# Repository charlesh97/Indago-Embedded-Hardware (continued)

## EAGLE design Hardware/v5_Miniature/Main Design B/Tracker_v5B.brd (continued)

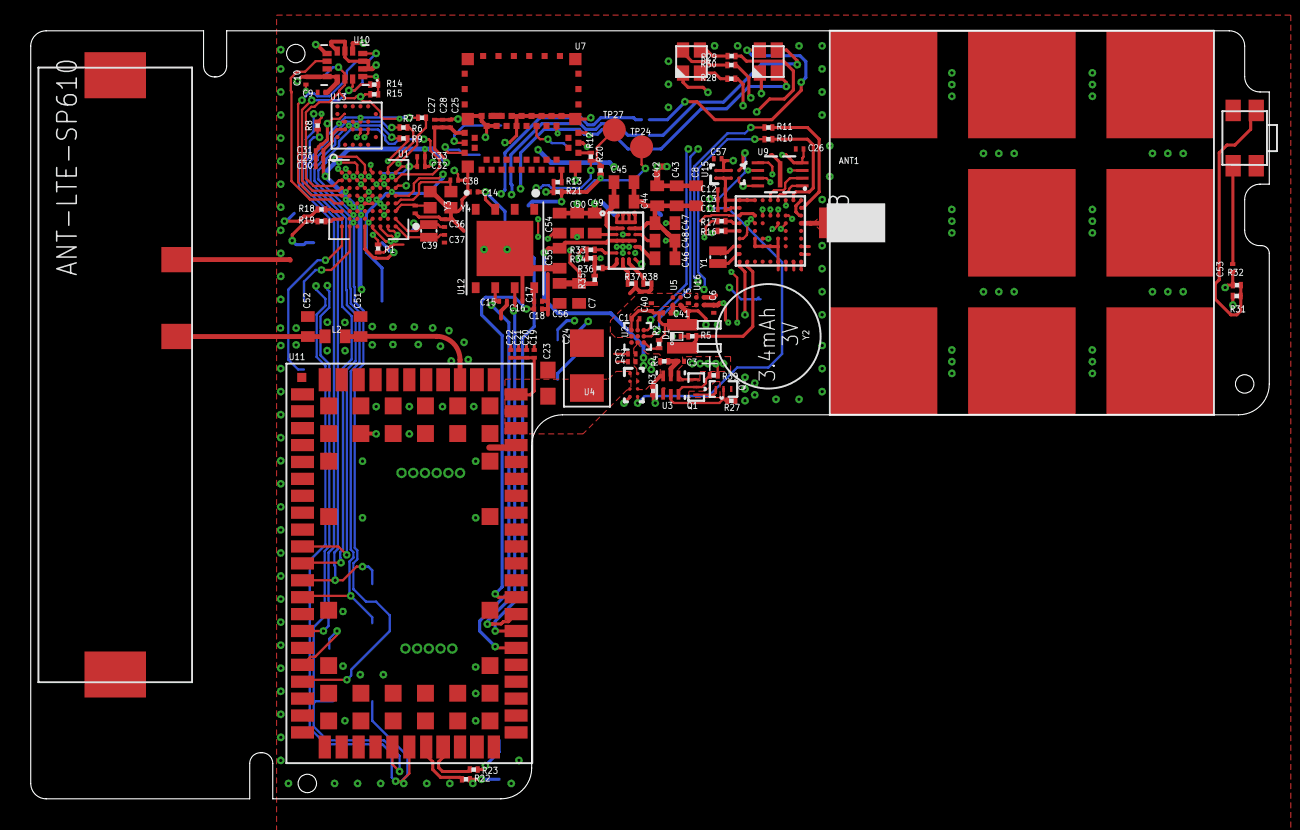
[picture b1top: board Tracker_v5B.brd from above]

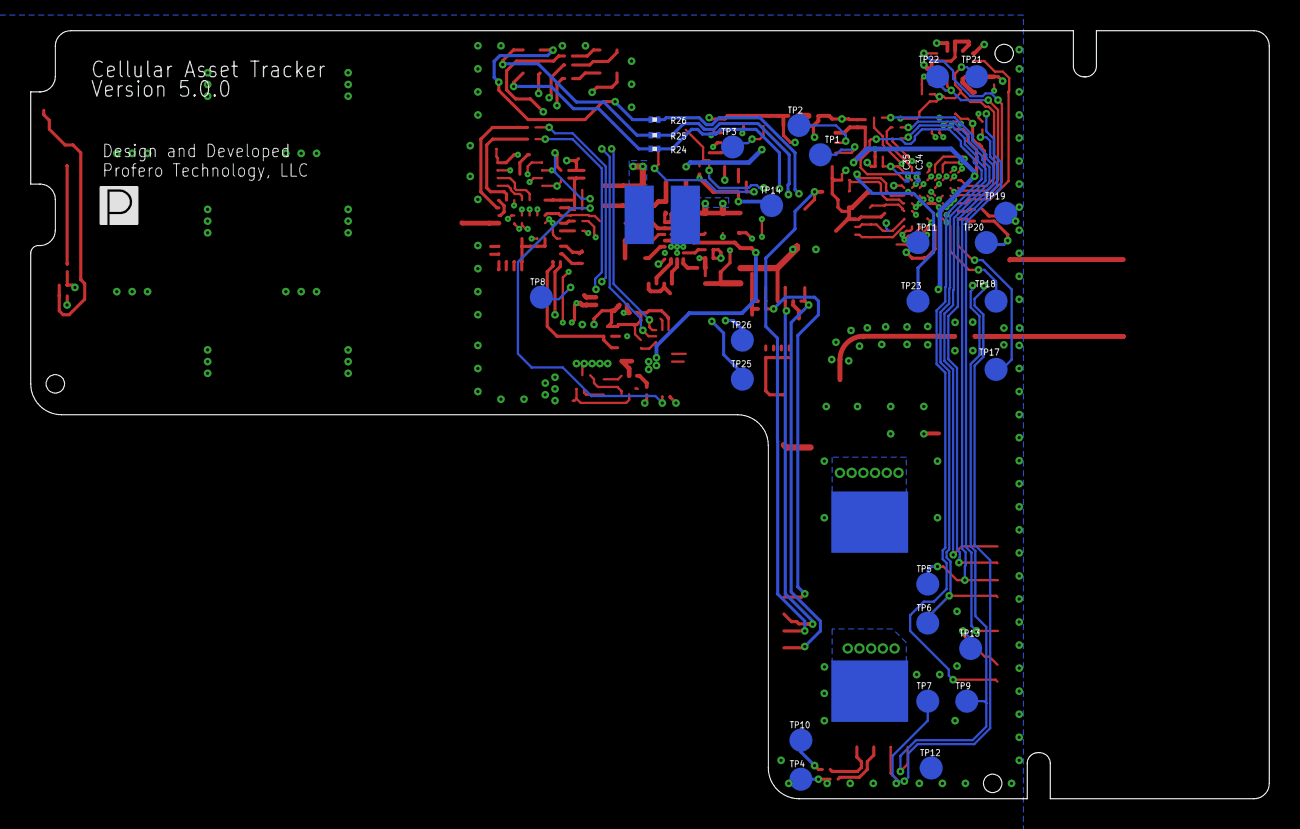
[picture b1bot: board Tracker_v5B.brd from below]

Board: 4 copper layers, 80.6 x 50.0 mm, 154 parts (33 on the bottom side), 124 nets.

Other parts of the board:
U$2: PROFERO-LOGO-SMALL

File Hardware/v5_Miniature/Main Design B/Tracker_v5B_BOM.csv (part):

"Qty";"Value";"Device";"Package";"Parts";"Description";"ALTERNATE_PARTNUMBER";"APPLICATION_BUILDNUMBER";"BOI";"BOI-METRIC";"BUILT_BY";"CATEGORY";"COMPTYPE";"COPYRIGHT";"CREATED_BY";"DESCRIPTION";"DESIG";"DIGI#";"DIGI-KEY_PART_NUMBER";"DIGI-KEY_PURCHASE_URL";"DIGIKEY_PART_NUMBER";"FAB";"ISP_PART";"MANF#";"MANUFACTURER";"MANUFACTURER_PART_NUMBER";"MF";"MOUNTTYPE";"MP";"MPN";"OPERATING_TEMP";"PACKAGE";"PACKAGEREFERENCE";"PARTNUMBER";"PART_STATUS";"PIN_COUNT";"POPULARITY";"REF";"REFDES";"ROHS";"ROHS_COMPLIANT";"SERIES";"SOURCELIBRARY";"SPICEPREFIX";"SUB-CATEGORY";"THERMALLOSS";"TP_SIGNAL_NAME";"TYPE";"URL";"VALUE";"VENDOR";"VOLTAGE_RATING";
"12";"0.1uF";"C-EUC0201";"C0201";"C2, C3, C9, C10, C11, C17, C22, C25, C26, C27, C32, C34";"CAPACITOR, European symbol";"";"";"";"";"";"";"";"";"";"";"";"";"";"";"";"";"";"";"";"";"";"";"";"";"";"";"";"";"";"";"0";"";"";"";"";"";"";"C";"";"";"";"";"";"";"";"";
"1";"0.47uF";"C-EUC0201";"C0201";"C1";"CAPACITOR, European symbol";"";"";"";"";"";"";"";"";"";"";"";"";"";"";"";"";"";"";"";"";"";"";"";"";"";"";"";"";"";"";"0";"";"";"";"";"";"";"C";"";"";"";"";"";"";"";"";
"1";"0ohm";"C-EUC0402";"C0402";"L2";"CAPACITOR, European symbol";"";"";"";"";"";"";"";"";"";"";"";"";"";"";"";"";"";"";"";"";"";"";"";"";"";"";"";"";"";"";"18";"";"";"";"";"";"";"C";"";"";"";"";"";"";"";"";
"1";"1.8nF";"C-EUC0402";"C0402";"C45";"CAPACITOR, European symbol";"";"";"";"";"";"";"";"";"";"";"";"";"";"";"";"";"";"";"";"";"";"";"";"";"";"";"";"";"";"";"18";"";"";"";"";"";"";"C";"";"";"";"";"";"";"";"";
"8";"100";"R-US_R0201";"R0201";"R6, R7, R8, R9, R12, R13, R16, R17";"RESISTOR, American symbol";"";"";"";"";"";"";"";"";"";"";"";"";"";"";"";"";"";"";"";"";"";"";"";"";"";"";"";"";"";"";"0";"";"";"";"";"";"";"R";"";"";"";"";"";"";"";"";
"7";"10000pF";"C-EUC0201";"C0201";"C13, C21, C29, C30, C31, C33, C35";"CAPACITOR, European symbol";"";"";"";"";"";"";"";"";"";"";"";"";"";"";"";"";"";"";"";"";"";"";"";"";"";"";"";"";"";"";"0";"";"";"";"";"";"";"C";"";"";"";"";"";"";"";"";
"3";"100k";"R-US_R0201";"R0201";"R1, R31, R32";"RESISTOR, American symbol";"";"";"";"";"";"";"";"";"";"";"";"";"";"";"";"";"";"";"";"";"";"";"";"";"";"";"";"";"";"";"0";"";"";"";"";"";"";"R";"";"";"";"";"";"";"";"";
"1";"100pF";"C-EUC0201";"C0201";"C53";"CAPACITOR, European symbol";"";"";"";"";"";"";"";"";"";"";"";"";"";"";"";"";"";"";"";"";"";"";"";"";"";"";"";"";"";"";"0";"";"";"";"";"";"";"C";"";"";"";"";"";"";"";"";
"1";"100pF";"C-EUC0402";"C0402";"C44";"CAPACITOR, European symbol";"";"";"";"";"";"";"";"";"";"";"";"";"";"";"";"";"";"";"";"";"";"";"";"";"";"";"";"";"";"";"18";"";"";"";"";"";"";"C";"";"";"";"";"";"";"";"";
"3";"10k";"R-US_R0201";"R0201";"R2, R33, R37";"RESISTOR, American symbol";"";"";"";"";"";"";"";"";"";"";"";"";"";"";"";"";"";"";"";"";"";"";"";"";"";"";"";"";"";"";"0";"";"";"";"";"";"";"R";"";"";"";"";"";"";"";"";
"2";"10nF";"C-EUC0402";"C0402";"C48, C49";"CAPACITOR, European symbol";"";"";"";"";"";"";"";"";"";"";"";"";"";"";"";"";"";"";"";"";"";"";"";"";"";"";"";"";"";"";"18";"";"";"";"";"";"";"C";"";"";"";"";"";"";"";"";
"2";"10pF";"C-EUC0201";"C0201";"C38, C39";"CAPACITOR, European symbol";"";"";"";"";"";"";"";"";"";"";"";"";"";"";"";"";"";"";"";"";"";"";"";"";"";"";"";"";"";"";"0";"";"";"";"";"";"";"C";"";"";"";"";"";"";"";"";
"1";"10uF";"C-EUC0402";"C0402";"C7";"CAPACITOR, European symbol";"";"";"";"";"";"";"";"";"";"";"";"";"";"";"";"";"";"";"";"";"";"";"";"";"";"";"";"";"";"";"18";"";"";"";"";"";"";"C";"";"";"";"";"";"";"";"";
"1";"10uF";"C-EUC0603";"C0603";"C23";"CAPACITOR, European symbol";"";"";"";"";"";"";"";"";"";"";"";"";"";"";"";"";"";"";"";"";"";"";"";"";"";"";"";"";"";"";"73";"";"";"";"";"";"";"C";"";"";"";"";"";"";"";"";
"2";"130";"R-US_R0201";"R0201";"R24, R28";"RESISTOR, American symbol";"";"";"";"";"";"";"";"";"";"";"";"";"";"";"";"";"";"";"";"";"";"";"";"";"";"";"";"";"";"";"0";"";"";"";"";"";"";"R";"";"";"";"";"";"";"";"";
"3";"15pF";"C-EUC0201";"C0201";"C19, C36, C37";"CAPACITOR, European symbol";"";"";"";"";"";"";"";"";"";"";"";"";"";"";"";"";"";"";"";"";"";"";"";"";"";"";"";"";"";"";"0";"";"";"";"";"";"";"C";"";"";"";"";"";"";"";"";
"1";"196ohm";"R-US_R0201";"R0201";"R34";"RESISTOR, American symbol";"";"";"";"";"";"";"";"";"";"";"";"";"";"";"";"";"";"";"";"";"";"";"";"";"";"";"";"";"";"";"0";"";"";"";"";"";"";"R";"";"";"";"";"";"";"";"";
"1";"1k";"R-US_R0201";"R0201";"R5";"RESISTOR, American symbol";"";"";"";"";"";"";"";"";"";"";"";"";"";"";"";"";"";"";"";"";"";"";"";"";"";"";"";"";"";"";"0";"";"";"";"";"";"";"R";"";"";"";"";"";"";"";"";
"8";"1uF";"C-EUC0201";"C0201";"C4, C5, C6, C12, C28, C40, C41, C57";"CAPACITOR, European symbol";"";"";"";"";"";"";"";"";"";"";"";"";"";"";"";"";"";"";"";"";"";"";"";"";"";"";"";"";"";"";"0";"";"";"";"";"";"";"C";"";"";"";"";"";"";"";"";
"2";"2.2uF";"C-EUC0402";"C0402";"C55, C56";"CAPACITOR, European symbol";"";"";"";"";"";"";"";"";"";"";"";"";"";"";"";"";"";"";"";"";"";"";"";"";"";"";"";"";"";"";"18";"";"";"";"";"";"";"C";"";"";"";"";"";"";"";"";
"1";"2.4k";"R-US_R0201";"R0201";"R38";"RESISTOR, American symbol";"";"";"";"";"";"";"";"";"";"";"";"";"";"";"";"";"";"";"";"";"";"";"";"";"";"";"";"";"";"";"0";"";"";"";"";"";"";"R";"";"";"";"";"";"";"";"";
"1";"20k";"R-US_R0201";"R0201";"R35";"RESISTOR, American symbol";"";"";"";"";"";"";"";"";"";"";"";"";"";"";"";"";"";"";"";"";"";"";"";"";"";"";"";"";"";"";"0";"";"";"";"";"";"";"R";"";"";"";"";"";"";"";"";
"2";"22nF";"C-EUC0402";"C0402";"C46, C54";"CAPACITOR, European symbol";"";"";"";"";"";"";"";"";"";"";"";"";"";"";"";"";"";"";"";"";"";"";"";"";"";"";"";"";"";"";"18";"";"";"";"";"";"";"C";"";"";"";"";"";"";"";"";
"4";"29";"R-US_R0201";"R0201";"R18, R19, R22, R23";"RESISTOR, American symbol";"";"";"";"";"";"";"";"";"";"";"";"";"";"";"";"";"";"";"";"";"";"";"";"";"";"";"";"";"";"";"0";"";"";"";"";"";"";"R";"";"";"";"";"";"";"";"";
"1";"2k";"R-US_R0201";"R0201";"R3";"RESISTOR, American symbol";"";"";"";"";"";"";"";"";"";"";"";"";"";"";"";"";"";"";"";"";"";"";"";"";"";"";"";"";"";"";"0";"";"";"";"";"";"";"R";"";"";"";"";"";"";"";"";
"4";"30";"R-US_R0201";"R0201";"R25, R26, R29, R30";"RESISTOR, American symbol";"";"";"";"";"";"";"";"";"";"";"";"";"";"";"";"";"";"";"";"";"";"";"";"";"";"";"";"";"";"";"0";"";"";"";"";"";"";"R";"";"";"";"";"";"";"";"";
"1";"330";"R-US_R0201";"R0201";"R4";"RESISTOR, American symbol";"";"";"";"";"";"";"";"";"";"";"";"";"";"";"";"";"";"";"";"";"";"";"";"";"";"";"";"";"";"";"0";"";"";"";"";"";"";"R";"";"";"";"";"";"";"";"";
"2";"4.7k";"R-US_R0201";"R0201";"R14, R15";"RESISTOR, American symbol";"";"";"";"";"";"";"";"";"";"";"";"";"";"";"";"";"";"";"";"";"";"";"";"";"";"";"";"";"";"";"0";"";"";"";"";"";"";"R";"";"";"";"";"";"";"";"";
"2";"470nF";"C-EUC0402";"C0402";"C47, C50";"CAPACITOR, European symbol";"";"";"";"";"";"";"";"";"";"";"";"";"";"";"";"";"";"";"";"";"";"";"";"";"";"";"";"";"";"";"18";"";"";"";"";"";"";"C";"";"";"";"";"";"";"";"";
"1";"47nF";"C-EUC0402";"C0402";"C43";"CAPACITOR, European symbol";"";"";"";"";"";"";"";"";"";"";"";"";"";"";"";"";"";"";"";"";"";"";"";"";"";"";"";"";"";"";"18";"";"";"";"";"";"";"C";"";"";"";"";"";"";"";"";
"4";"47pF";"C-EUC0201";"C0201";"C14, C15, C16, C18";"CAPACITOR, European symbol";"";"";"";"";"";"";"";"";"";"";"";"";"";"";"";"";"";"";"";"";"";"";"";"";"";"";"";"";"";"";"0";"";"";"";"";"";"";"C";"";"";"";"";"";"";"";"";
"2";"5M";"R-US_R0201";"R0201";"R27, R39";"RESISTOR, American symbol";"";"";"";"";"";"";"";"";"";"";"";"";"";"";"";"";"";"";"";"";"";"";"";"";"";"";"";"";"";"";"0";"";"";"";"";"";"";"R";"";"";"";"";"";"";"";"";
"2";"68nF";"C-EUC0402";"C0402";"C8, C42";"CAPACITOR, European symbol";"";"";"";"";"";"";"";"";"";"";"";"";"";"";"";"";"";"";"";"";"";"";"";"";"";"";"";"";"";"";"18";"";"";"";"";"";"";"C";"";"";"";"";"";"";"";"";
"1";"68pF";"C-EUC0201";"C0201";"C20";"CAPACITOR, European symbol";"";"";"";"";"";"";"";"";"";"";"";"";"";"";"";"";"";"";"";"";"";"";"";"";"";"";"";"";"";"";"0";"";"";"";"";"";"";"C";"";"";"";"";"";"";"";"";
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
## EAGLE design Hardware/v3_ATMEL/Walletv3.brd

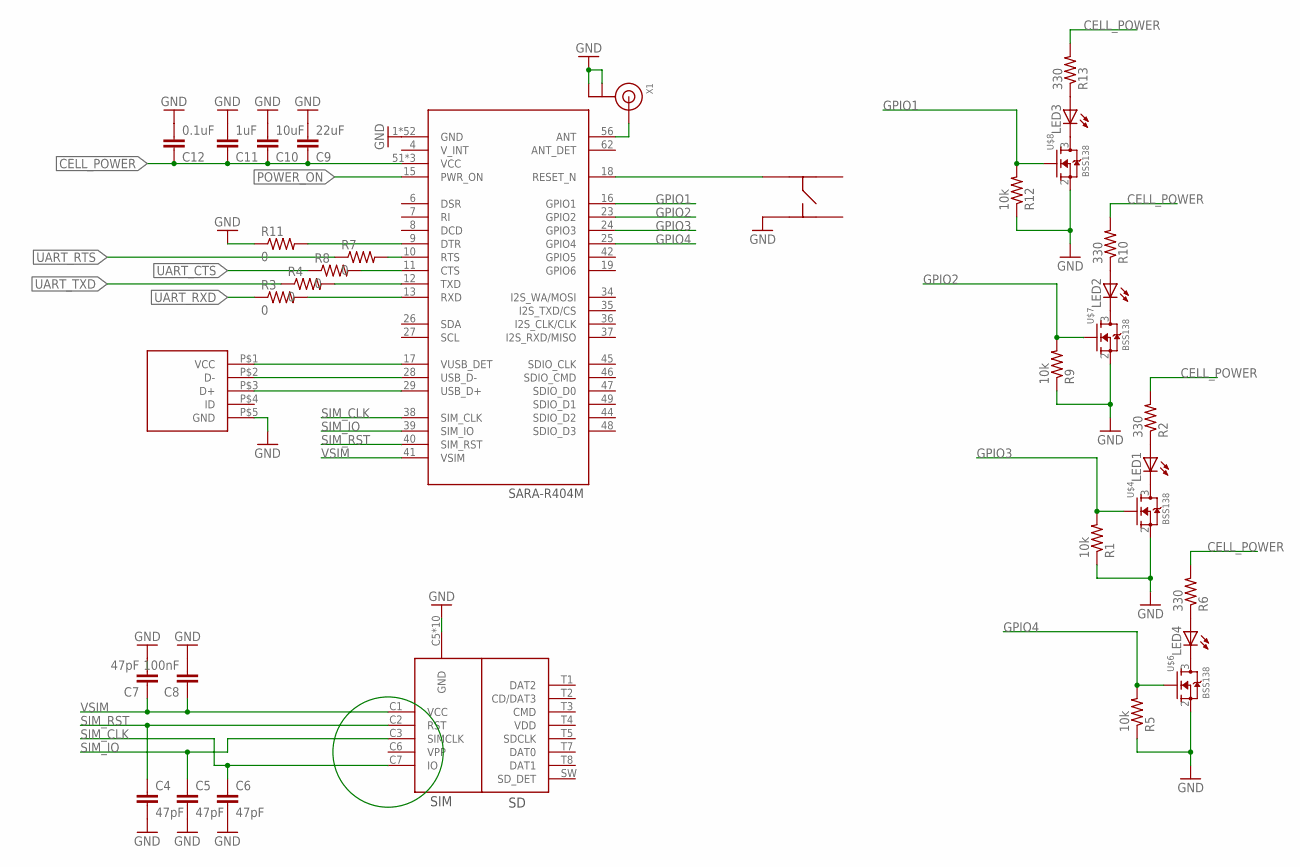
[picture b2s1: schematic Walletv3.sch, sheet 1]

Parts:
C4, C5, C6, C7: 47pF; C0402
C8: 100nF; C0402
C9: 22uF; C0805
C10: 10uF; C0603
C11: 1uF; C0402
C12: 0.1uF; C0402
LED1, LED2, LED3, LED4: LEDCHIPLED_0603; CHIPLED_0603
R1, R5, R9, R12: 10k; R0402
R2, R6, R10, R13: 330; R0402
R3, R4, R7, R8, R11: 0; R0402
U$2: SIM_SD_MOLEX
U$3: SARA-R404M
U$4, U$6, U$7, U$8: BSS138; SOT23-3
U$5: MICRO_USB; MOLEX_USB
U$9: KMR731NG
X1: ANTENNA_U.FL; U.FL

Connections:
CELL_POWER: C9.1, C10.1, C11.1, C12.1, R2.2, R6.2, R10.2, R13.2, U$3.51 (VCC), U$3.52 (VCC), U$3.53 (VCC); also elsewhere on the board
GND: C4.2, C5.2, C6.2, C7.2, C8.2, C9.2, C10.2, C11.2, C12.2, R1.1, R5.1, R9.1, R11.1, R12.1, U$2.C5 (GND), U$2.G1 (GND), U$2.G2 (GND), U$2.G3 (GND), U$2.G4 (GND), U$2.G5 (GND), U$2.G6 (GND), U$2.G7 (GND), U$2.G8 (GND), U$2.T6 (GND), U$3.1 (GND), U$3.3 (GND), U$3.5 (GND), U$3.14 (GND), U$3.20 (GND), U$3.21 (GND), U$3.22 (GND), U$3.30 (GND), U$3.32 (GND), U$3.43 (GND), U$3.50 (GND), U$3.54 (GND), U$3.55 (GND), U$3.57 (GND), U$3.58 (GND), U$3.59 (GND), U$3.60 (GND), U$3.61 (GND), U$3.63 (GND), U$3.64 (GND), U$3.65 (GND), U$3.66 (GND), U$3.67 (GND), U$3.68 (GND), U$3.69 (GND), U$3.70 (GND), U$3.71 (GND), U$3.72 (GND), U$3.73 (GND), U$3.74 (GND), U$3.75 (GND), U$3.76 (GND), U$3.77 (GND), U$3.78 (GND), U$3.79 (GND), U$3.80 (GND), U$3.81 (GND), U$3.82 (GND), U$3.83 (GND), U$3.84 (GND), U$3.85 (GND), U$3.86 (GND), U$3.87 (GND), U$3.88 (GND), U$3.89 (GND), U$3.90 (GND), U$3.91 (GND), U$3.92 (GND), U$3.93 (GND), U$3.94 (GND), U$3.95 (GND), U$3.96 (GND), U$4.2 (S), U$5.P$5 (GND), U$6.2 (S), U$7.2 (S), U$8.2 (S), U$9.P$4, X1.1 (GND), X1.2 (GND); also elsewhere on the board
GPIO1: R12.2, U$3.16 (GPIO1), U$8.1 (G)
GPIO2: R9.2, U$3.23 (GPIO2), U$7.1 (G)
GPIO3: R1.2, U$3.24 (GPIO3), U$4.1 (G)
GPIO4: R5.2, U$3.25 (GPIO4), U$6.1 (G)
unnamed: U$3.17 (VUSB_DET), U$5.P$1 (VCC)
unnamed: U$3.28 (USB_D-), U$5.P$2 (D-)
unnamed: U$3.29 (USB_D+), U$5.P$3 (D+)
unnamed: LED1.C, U$4.3 (D)
unnamed: U$3.18 (RESET_N), U$9.P$1
unnamed: LED1.A, R2.1
unnamed: R4.2, U$3.12 (TXD)
unnamed: R3.2, U$3.13 (RXD)
unnamed: LED2.C, U$7.3 (D)
unnamed: LED2.A, R10.1
unnamed: U$3.56 (ANT), X1.3 (SIGNAL)
unnamed: R11.2, U$3.9 (DTR)
unnamed: LED4.C, U$6.3 (D)
unnamed: LED4.A, R6.1
unnamed: LED3.C, U$8.3 (D)
unnamed: R8.2, U$3.11 (CTS)
unnamed: R7.2, U$3.10 (RTS)
unnamed: LED3.A, R13.1
POWER_ON: U$3.15 (PWR_ON); also elsewhere on the board
SIM_CLK: C6.1, U$2.C7 (IO), U$3.38 (SIM_CLK)
SIM_IO: C5.1, U$2.C3 (SIMCLK), U$3.39 (SIM_IO)
SIM_RST: C4.1, U$2.C2 (RST), U$3.40 (SIM_RST)
UART_CTS: R8.1; also elsewhere on the board
UART_RTS: R7.1; also elsewhere on the board
UART_RXD: R3.1; also elsewhere on the board
UART_TXD: R4.1; also elsewhere on the board
VSIM: C7.1, C8.1, U$2.C1 (VCC), U$3.41 (VSIM)

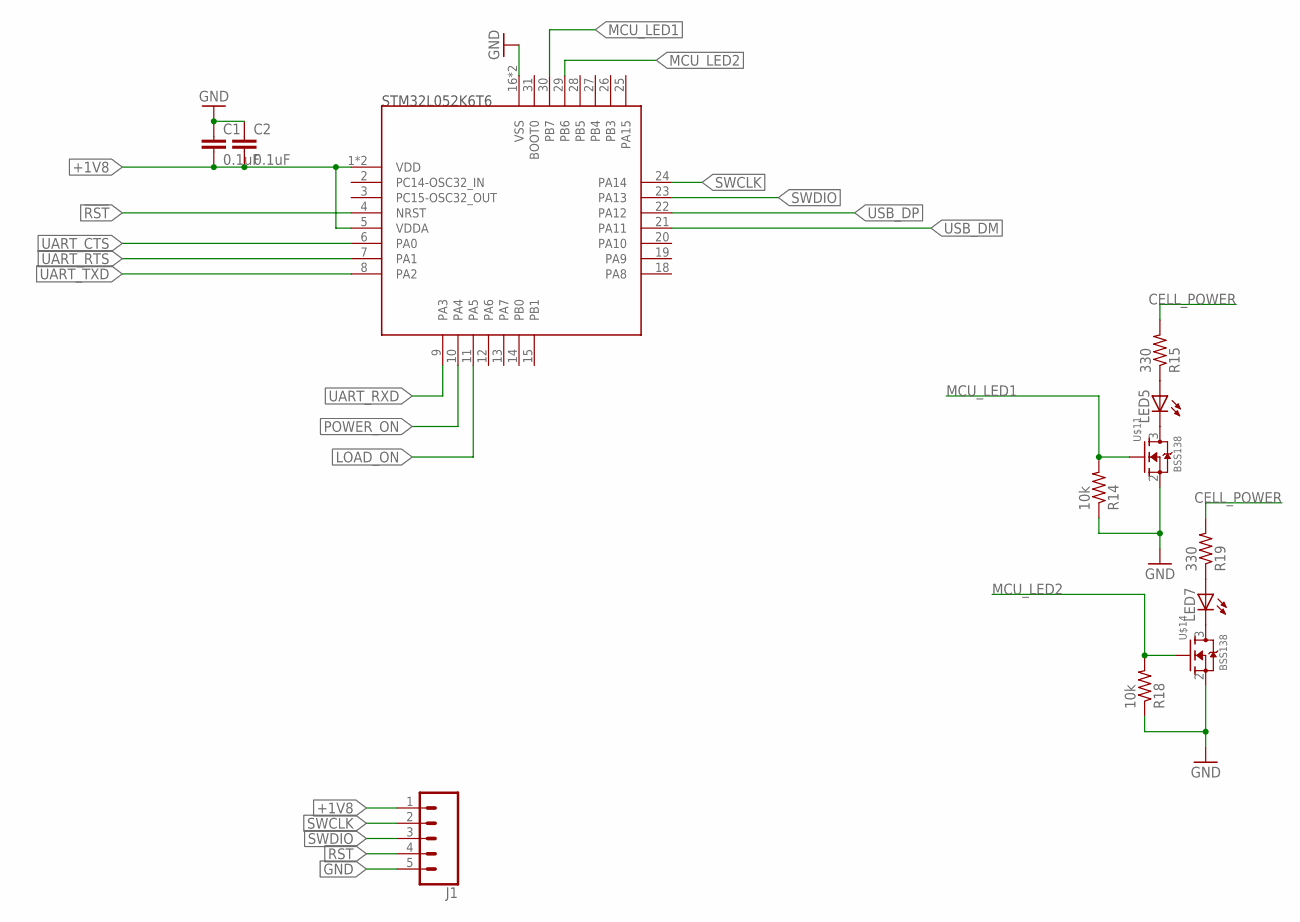
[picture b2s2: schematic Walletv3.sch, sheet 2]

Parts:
C1, C2: 0.1uF; C0402
J1: CONN_05; 1X05
LED5, LED7: LEDCHIPLED_0603; CHIPLED_0603
R14, R18: 10k; R0402
R15, R19: 330; R0402
U$1: STM32L052K6T6LQFP32-7X7; QFP80P900X900X160-32
U$11, U$14: BSS138; SOT23-3

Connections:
!RST: J1.4, U$1.4 (NRST)
+1V8: C1.2, C2.2, J1.1, U$1.1 (VDD), U$1.5 (VDDA), U$1.17 (VDD); also elsewhere on the board
CELL_POWER: R15.2, R19.2; also elsewhere on the board
GND: C1.1, C2.1, J1.5, R14.1, R18.1, U$1.16 (VSS), U$1.32 (VSS), U$11.2 (S), U$14.2 (S); also elsewhere on the board
LOAD_ON: U$1.11 (PA5); also elsewhere on the board
MCU_LED1: R14.2, U$1.30 (PB7), U$11.1 (G)
MCU_LED2: R18.2, U$1.29 (PB6), U$14.1 (G)
unnamed: LED5.C, U$11.3 (D)
unnamed: LED5.A, R15.1
unnamed: LED7.C, U$14.3 (D)
unnamed: LED7.A, R19.1
POWER_ON: U$1.10 (PA4); also elsewhere on the board
SWCLK: J1.2, U$1.24 (PA14)
SWDIO: J1.3, U$1.23 (PA13)
UART_CTS: U$1.6 (PA0); also elsewhere on the board
UART_RTS: U$1.7 (PA1); also elsewhere on the board
UART_RXD: U$1.9 (PA3); also elsewhere on the board
UART_TXD: U$1.8 (PA2); also elsewhere on the board
USB_DM: U$1.21 (PA11)
USB_DP: U$1.22 (PA12)

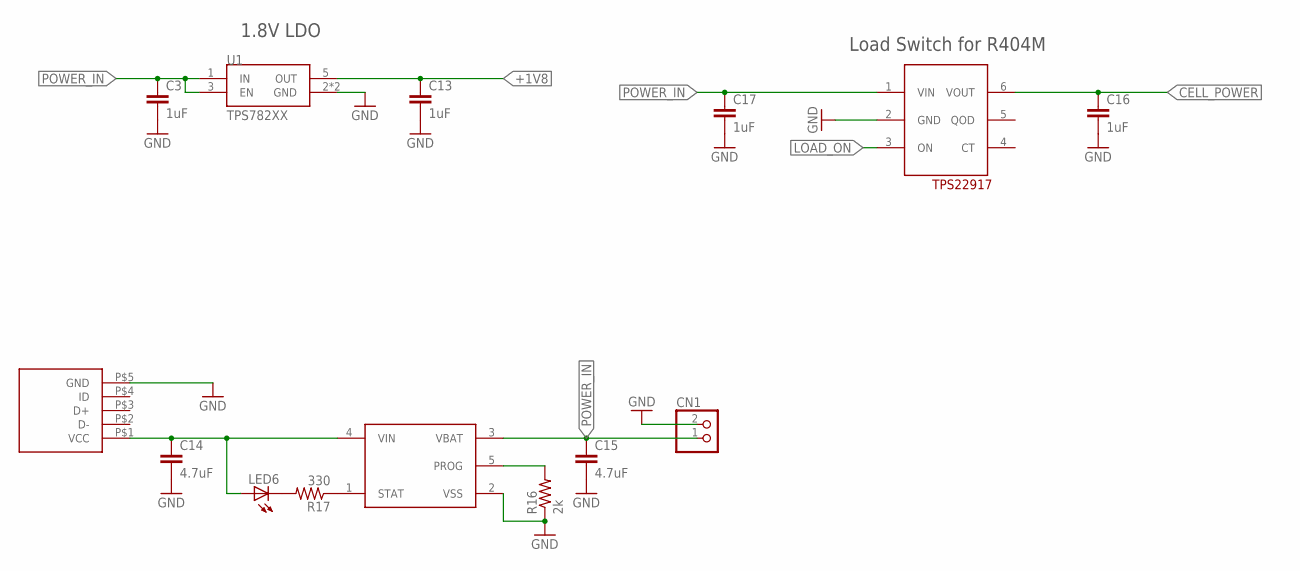
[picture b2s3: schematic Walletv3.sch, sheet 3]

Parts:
C3, C13, C16, C17: 1uF; C0402
C14, C15: 4.7uF; C0603
CN1: JST_2PIN-SMT-RA; JST-PH-2-SMT-RA
LED6: LEDCHIP-LED0603; CHIP-LED0603
R16: 2k; R0402
R17: 330; R0402
U1: TPS782XX; SOT23-5L
U$10: TPS22917; SOT23-6
U$12: MICRO_USB; MOLEX_USB
U$13: MCP73831; SOT23-5L

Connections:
+1V8: C13.1, U1.5 (OUT); also elsewhere on the board
CELL_POWER: C16.1, U$10.6 (VOUT); also elsewhere on the board
GND: C3.2, C13.2, C14.2, C15.2, C16.2, C17.2, CN1.2 (1), R16.1, U1.2 (GND), U1.4 (GND), U$10.2 (GND), U$12.P$5 (GND), U$13.2 (VSS); also elsewhere on the board
LOAD_ON: U$10.3 (ON); also elsewhere on the board
unnamed: C14.1, LED6.A, U$12.P$1 (VCC), U$13.4 (VIN)
unnamed: R16.2, U$13.5 (PROG)
unnamed: R17.1, U$13.1 (STAT)
unnamed: LED6.C, R17.2
POWER_IN: C3.1, C15.1, C17.1, CN1.1 (2), U1.1 (IN), U1.3 (EN), U$10.1 (VIN), U$13.3 (VBAT)

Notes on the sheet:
1.8V LDO
Load Switch for R404M

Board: 4 copper layers, 61 parts (12 on the bottom side), 49 nets, no tracks yet.

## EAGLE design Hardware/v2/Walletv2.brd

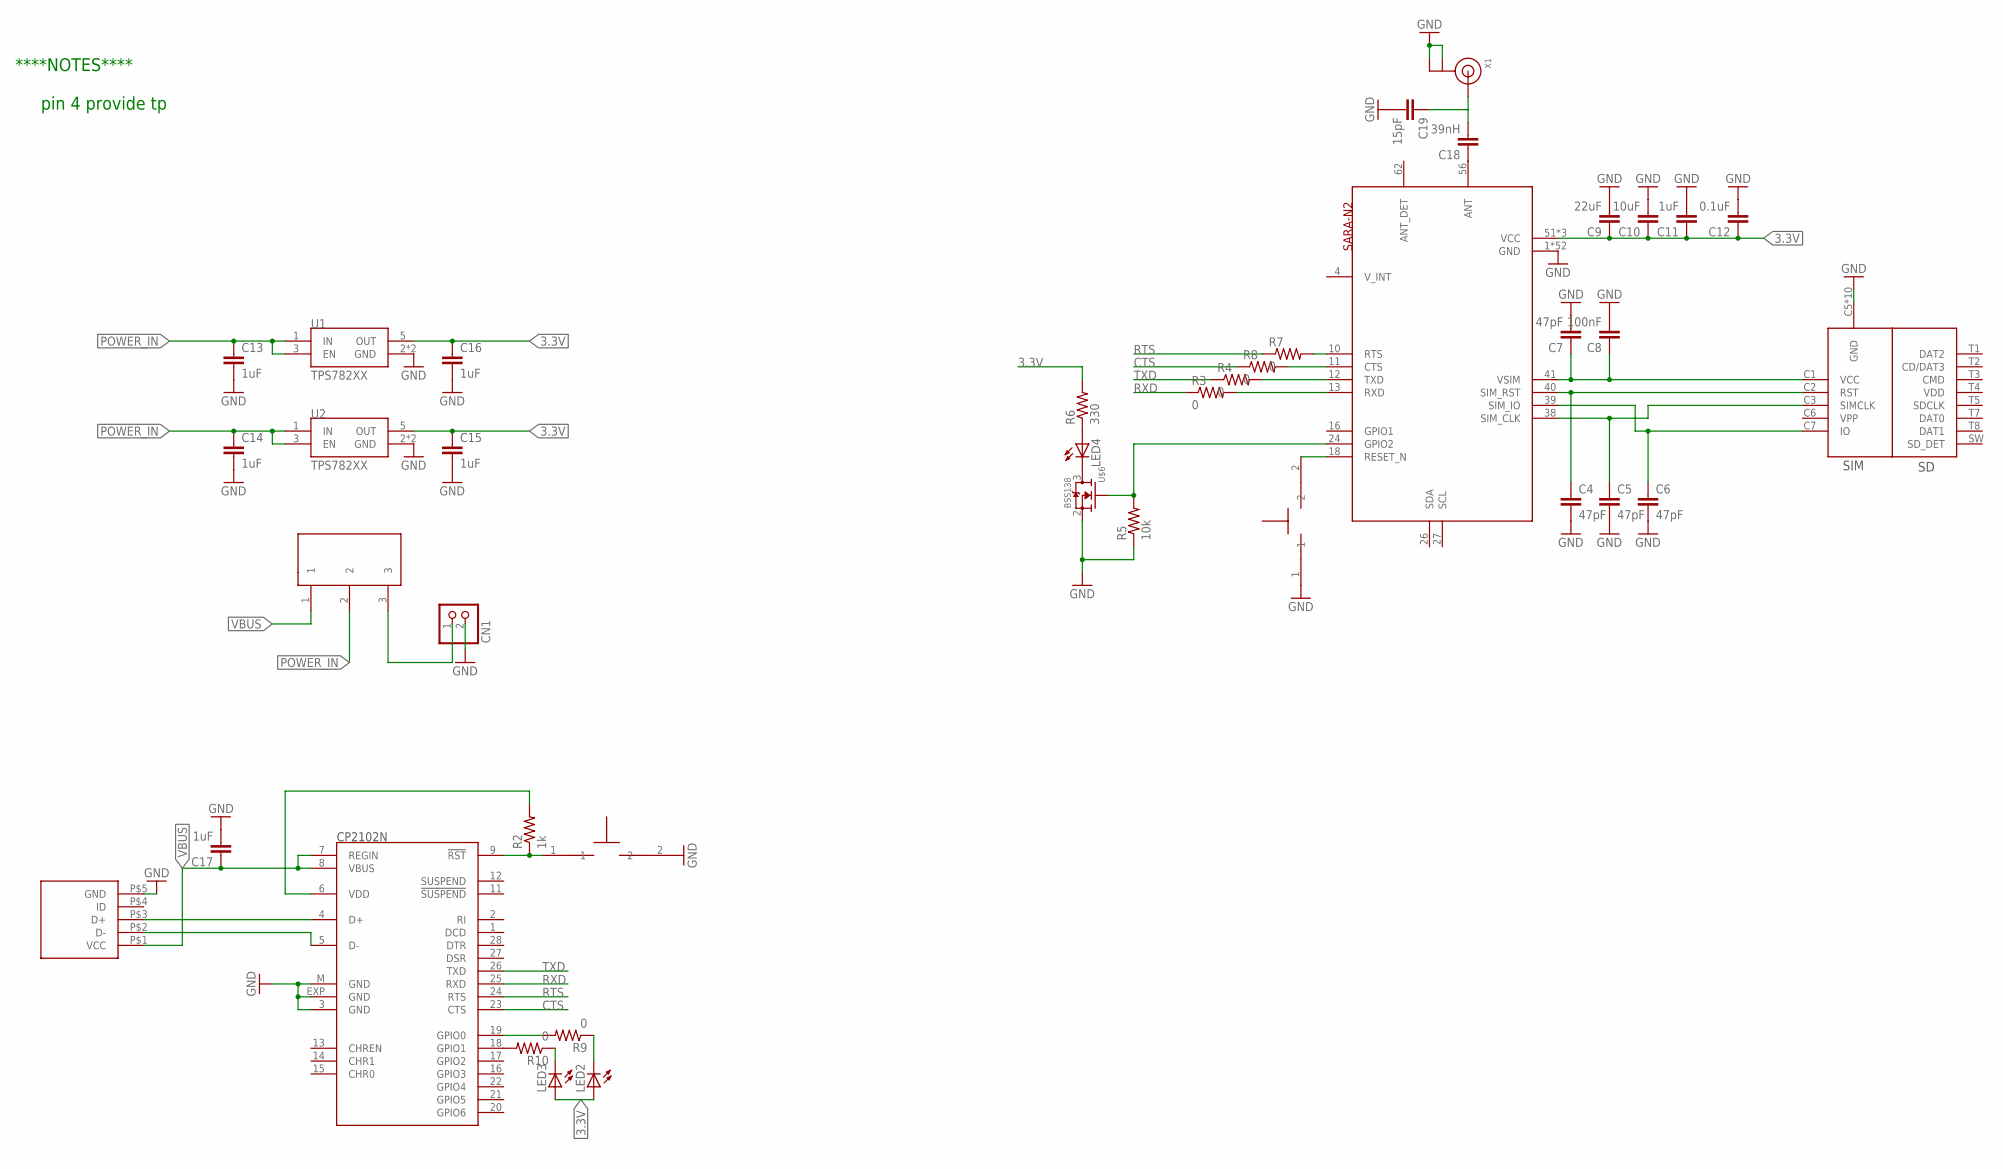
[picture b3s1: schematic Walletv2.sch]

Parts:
C4, C5, C6, C7: 47pF; C0402
C8: 100nF; C0402
C9: 22uF; C0805
C10: 10uF; C0603
C11, C13, C14, C15, C16, C17: 1uF; C0402
C12: 0.1uF; C0402
C18: 39nH; C0402
C19: 15pF; C0402
CN1: JST_2PIN-SMT-RA; JST-PH-2-SMT-RA
IC1: CP2102; MLP28
LED2, LED3, LED4: LEDCHIPLED_0603; CHIPLED_0603
R2: 1k; R0402
R3, R4, R7, R8, R9, R10: 0; R0402
R5: 10k; R0402
R6: 330; R0402
S1, S2: TACTILE_SKRKA
U1, U2: TPS782XX; SOT23-5L
U$1: SARA-N2
U$2: SIM_SD_MOLEX
U$4: SPDT_THRU
U$5: MICRO_USB; MOLEX_USB
U$6: BSS138; SOT23-3
X1: ANTENNA_U.FL; U.FL

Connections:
3.3V: C9.1, C10.1, C11.1, C12.1, C15.1, C16.1, LED2.A, LED3.A, R6.2, U1.5 (OUT), U2.5 (OUT), U$1.51 (VCC), U$1.52 (VCC), U$1.53 (VCC)
CTS: IC1.23 (CTS), R8.1
D_N: IC1.5 (D-), U$5.P$2 (D-)
D_P: IC1.4 (D+), U$5.P$3 (D+)
GND: C4.2, C5.2, C6.2, C7.2, C8.2, C9.2, C10.2, C11.2, C12.2, C13.2, C14.2, C15.2, C16.2, C17.2, C19.2, CN1.2 (1), IC1.3 (GND), IC1.EXP (GND), IC1.M (GND), R5.1, S1.2, S2.1, U1.2 (GND), U1.4 (GND), U2.2 (GND), U2.4 (GND), U$1.1 (GND), U$1.3 (GND), U$1.5 (GND), U$1.14 (GND), U$1.20 (GND), U$1.21 (GND), U$1.22 (GND), U$1.30 (GND), U$1.32 (GND), U$1.43 (GND), U$1.50 (GND), U$1.54 (GND), U$1.55 (GND), U$1.57 (GND), U$1.58 (GND), U$1.59 (GND), U$1.60 (GND), U$1.61 (GND), U$1.63 (GND), U$1.64 (GND), U$1.65 (GND), U$1.66 (GND), U$1.67 (GND), U$1.68 (GND), U$1.69 (GND), U$1.70 (GND), U$1.71 (GND), U$1.72 (GND), U$1.73 (GND), U$1.74 (GND), U$1.75 (GND), U$1.76 (GND), U$1.77 (GND), U$1.78 (GND), U$1.79 (GND), U$1.80 (GND), U$1.81 (GND), U$1.82 (GND), U$1.83 (GND), U$1.84 (GND), U$1.85 (GND), U$1.86 (GND), U$1.87 (GND), U$1.88 (GND), U$1.89 (GND), U$1.90 (GND), U$1.91 (GND), U$1.92 (GND), U$1.93 (GND), U$1.94 (GND), U$1.95 (GND), U$1.96 (GND), U$2.C5 (GND), U$2.G1 (GND), U$2.G2 (GND), U$2.G3 (GND), U$2.G4 (GND), U$2.G5 (GND), U$2.G6 (GND), U$2.G7 (GND), U$2.G8 (GND), U$2.T6 (GND), U$5.P$5 (GND), U$6.2 (S), X1.1 (GND), X1.2 (GND)
unnamed: C18.1, U$1.56 (ANT)
unnamed: C7.1, C8.1, U$1.41 (VSIM), U$2.C1 (VCC)
unnamed: C4.1, U$1.40 (SIM_RST), U$2.C2 (RST)
unnamed: C6.1, U$1.39 (SIM_IO), U$2.C7 (IO)
unnamed: C5.1, U$1.38 (SIM_CLK), U$2.C3 (SIMCLK)
unnamed: S2.2, U$1.18 (RESET_N)
unnamed: R4.2, U$1.12 (TXD)
unnamed: R3.2, U$1.13 (RXD)
unnamed: IC1.9 (!RST), R2.1, S1.1
unnamed: LED2.C, R9.1
unnamed: CN1.1 (2), U$4.3
unnamed: IC1.6 (VDD), R2.2
unnamed: IC1.18 (GPIO1), R10.2
unnamed: LED4.C, U$6.3 (D)
unnamed: LED4.A, R6.1
unnamed: R5.2, U$1.24 (GPIO2), U$6.1 (G)
unnamed: LED3.C, R10.1
unnamed: R8.2, U$1.11 (CTS)
unnamed: R7.2, U$1.10 (RTS)
unnamed: IC1.19 (GPIO0), R9.2
unnamed: C18.2, C19.1, X1.3 (SIGNAL)
POWER_IN: C13.1, C14.1, U1.1 (IN), U1.3 (EN), U2.1 (IN), U2.3 (EN), U$4.2
RTS: IC1.24 (RTS), R7.1
RXD: IC1.25 (RXD), R3.1
TXD: IC1.26 (TXD), R4.1
VBUS: C17.1, IC1.7 (REGIN), IC1.8 (VBUS), U$4.1, U$5.P$1 (VCC)

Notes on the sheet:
pin 4 provide tp
****NOTES****

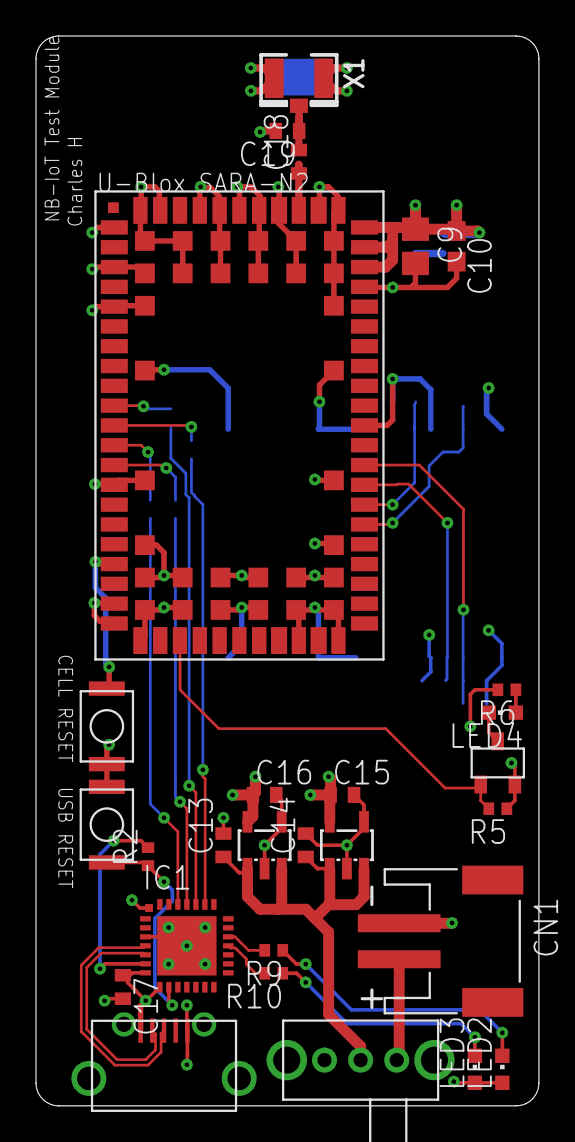
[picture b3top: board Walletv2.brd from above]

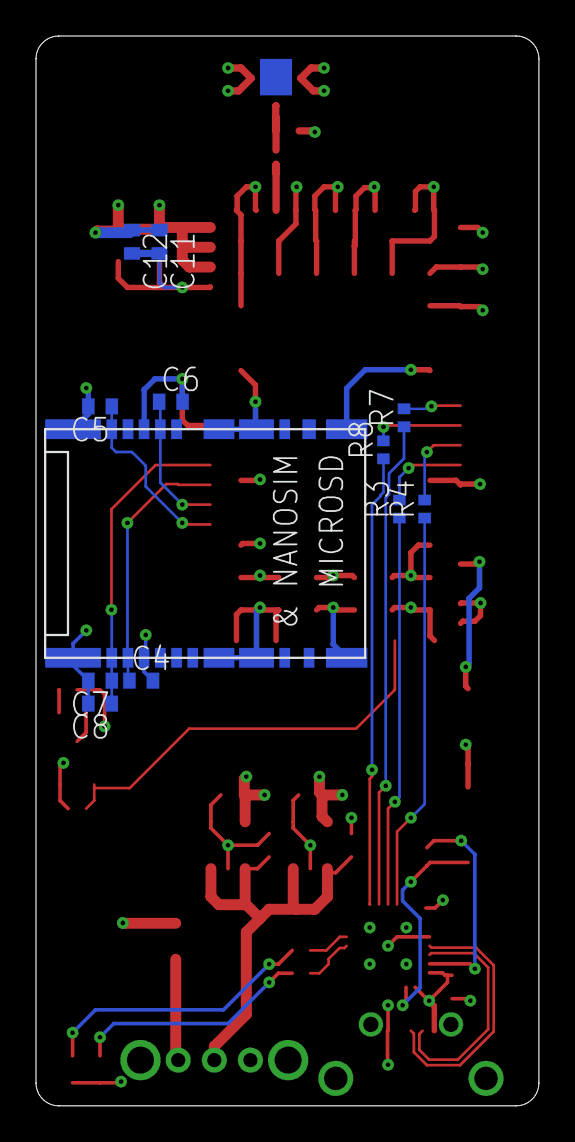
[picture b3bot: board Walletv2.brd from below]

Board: 4 copper layers, 27.9 x 59.4 mm, 40 parts (12 on the bottom side), 31 nets.

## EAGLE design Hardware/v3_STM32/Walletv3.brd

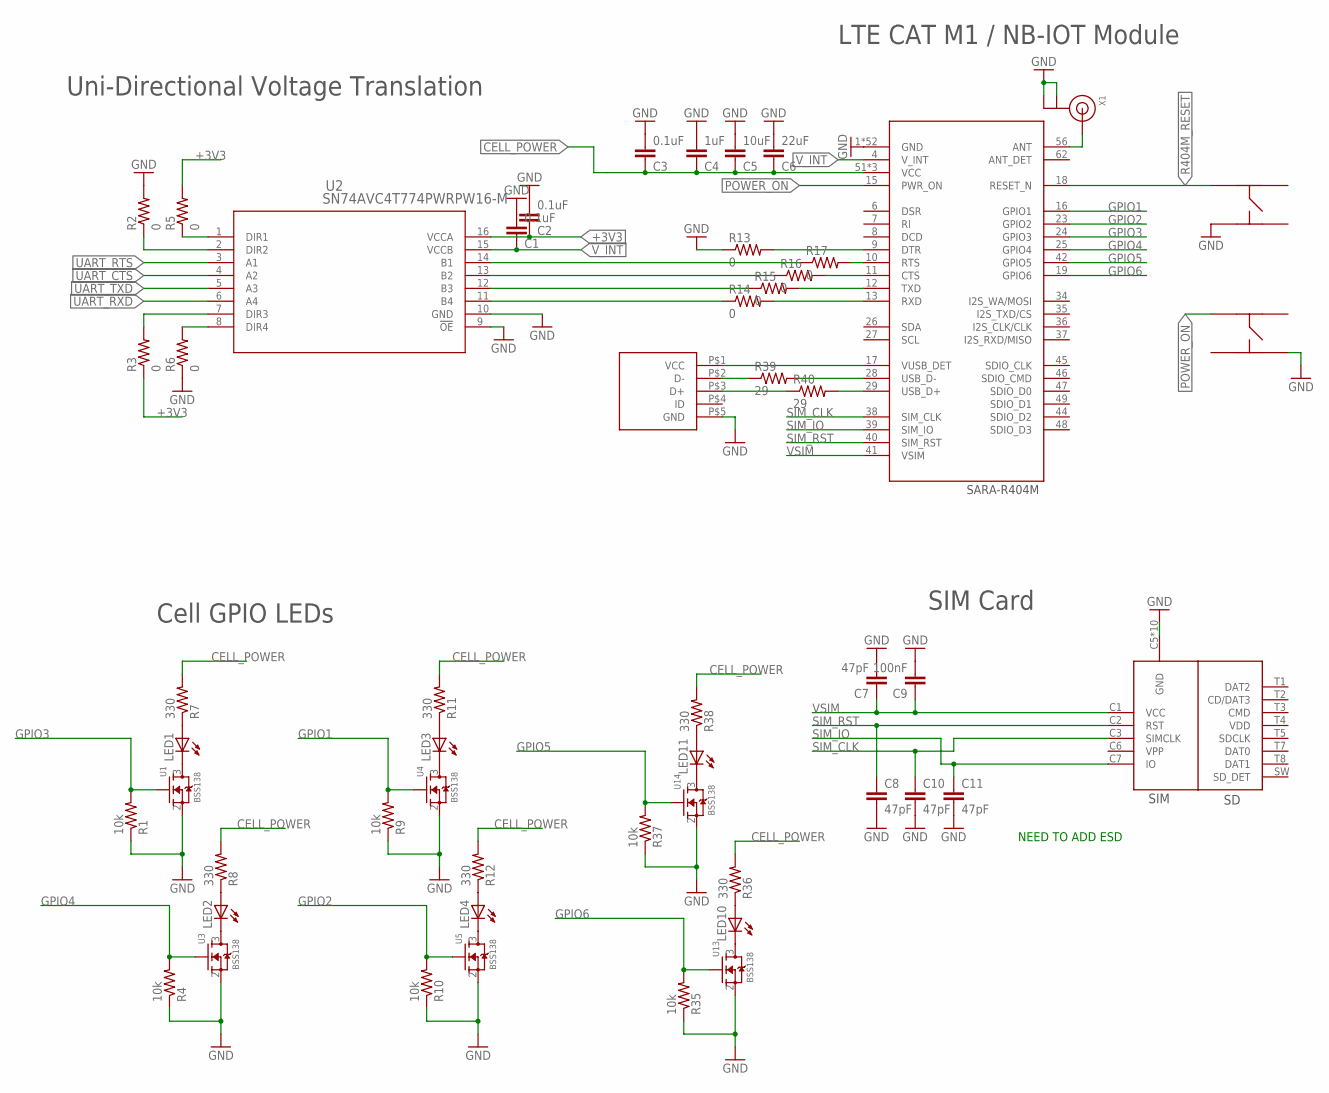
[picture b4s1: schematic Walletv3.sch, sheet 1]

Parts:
C1, C2, C3: 0.1uF; C0402
C4: 1uF; C0402
C5: 10uF; C0603
C6: 22uF; C0805
C7, C8, C10, C11: 47pF; C0402
C9: 100nF; C0402
LED1, LED2, LED3, LED4, LED10, LED11: LEDCHIPLED_0603; CHIPLED_0603
R1, R4, R9, R10, R35, R37: 10k; R0402
R2, R3, R5, R6, R13, R14, R15, R16, R17: 0; R0402
R7, R8, R11, R12, R36, R38: 330; R0402
R39, R40: 29; R0402
S1, S2: KMR731NG
U1, U3, U4, U5, U13, U14: BSS138; SOT23-3
U2: SN74AVC4T774PWRPW16-M; PW16-M
U6: SARA-R404M
U$1: SIM_SD_MOLEX
U$2: MICRO_USB; MOLEX_USB
X1: ANTENNA_U.FL; U.FL

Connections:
+3V3: C2.1, R3.1, R5.2, U2.16 (VCCA); also elsewhere on the board
CELL_POWER: C3.1, C4.1, C5.1, C6.1, R7.2, R8.2, R11.2, R12.2, R36.2, R38.2, U6.51 (VCC), U6.52 (VCC), U6.53 (VCC); also elsewhere on the board
GND: C1.2, C2.2, C3.2, C4.2, C5.2, C6.2, C7.2, C8.2, C9.2, C10.2, C11.2, R1.1, R2.2, R4.1, R6.1, R9.1, R10.1, R13.1, R35.1, R37.1, S1.P$4, S2.P$3, U1.2 (S), U2.9 (!OE), U2.10 (GND), U3.2 (S), U4.2 (S), U5.2 (S), U6.1 (GND), U6.3 (GND), U6.5 (GND), U6.14 (GND), U6.20 (GND), U6.21 (GND), U6.22 (GND), U6.30 (GND), U6.32 (GND), U6.43 (GND), U6.50 (GND), U6.54 (GND), U6.55 (GND), U6.57 (GND), U6.58 (GND), U6.59 (GND), U6.60 (GND), U6.61 (GND), U6.63 (GND), U6.64 (GND), U6.65 (GND), U6.66 (GND), U6.67 (GND), U6.68 (GND), U6.69 (GND), U6.70 (GND), U6.71 (GND), U6.72 (GND), U6.73 (GND), U6.74 (GND), U6.75 (GND), U6.76 (GND), U6.77 (GND), U6.78 (GND), U6.79 (GND), U6.80 (GND), U6.81 (GND), U6.82 (GND), U6.83 (GND), U6.84 (GND), U6.85 (GND), U6.86 (GND), U6.87 (GND), U6.88 (GND), U6.89 (GND), U6.90 (GND), U6.91 (GND), U6.92 (GND), U6.93 (GND), U6.94 (GND), U6.95 (GND), U6.96 (GND), U13.2 (S), U14.2 (S), U$1.C5 (GND), U$1.G1 (GND), U$1.G2 (GND), U$1.G3 (GND), U$1.G4 (GND), U$1.G5 (GND), U$1.G6 (GND), U$1.G7 (GND), U$1.G8 (GND), U$1.T6 (GND), U$2.P$5 (GND), X1.1 (GND), X1.2 (GND); also elsewhere on the board
GPIO1: R9.2, U4.1 (G), U6.16 (GPIO1)
GPIO2: R10.2, U5.1 (G), U6.23 (GPIO2)
GPIO3: R1.2, U1.1 (G), U6.24 (GPIO3)
GPIO4: R4.2, U3.1 (G), U6.25 (GPIO4)
GPIO5: R37.2, U6.42 (GPIO5), U14.1 (G)
GPIO6: R35.2, U6.19 (GPIO6), U13.1 (G)
unnamed: U6.17 (VUSB_DET), U$2.P$1 (VCC)
unnamed: R39.1, U$2.P$2 (D-)
unnamed: R40.1, U$2.P$3 (D+)
unnamed: LED1.C, U1.3 (D)
unnamed: R2.1, U2.2 (DIR2)
unnamed: LED1.A, R7.1
unnamed: R15.2, U6.12 (TXD)
unnamed: R14.2, U6.13 (RXD)
unnamed: LED4.C, U5.3 (D)
unnamed: LED4.A, R12.1
unnamed: U6.56 (ANT), X1.3 (SIGNAL)
unnamed: R13.2, U6.9 (DTR)
unnamed: LED2.C, U3.3 (D)
unnamed: LED2.A, R8.1
unnamed: LED3.C, U4.3 (D)
unnamed: R16.2, U6.11 (CTS)
unnamed: R17.2, U6.10 (RTS)
unnamed: LED3.A, R11.1
unnamed: R17.1, U2.14 (B1)
unnamed: R16.1, U2.13 (B2)
unnamed: R15.1, U2.12 (B3)
unnamed: R14.1, U2.11 (B4)
unnamed: R5.1, U2.1 (DIR1)
unnamed: R3.2, U2.7 (DIR3)
unnamed: R6.2, U2.8 (DIR4)
unnamed: LED10.C, U13.3 (D)
unnamed: LED10.A, R36.1
unnamed: LED11.C, U14.3 (D)
unnamed: LED11.A, R38.1
unnamed: R39.2, U6.28 (USB_D-)
unnamed: R40.2, U6.29 (USB_D+)
POWER_ON: S2.P$1, U6.15 (PWR_ON); also elsewhere on the board
R404M_RESET: S1.P$1, U6.18 (RESET_N); also elsewhere on the board
SIM_CLK: C10.1, U6.38 (SIM_CLK), U$1.C3 (SIMCLK)
SIM_IO: C11.1, U6.39 (SIM_IO), U$1.C7 (IO)
SIM_RST: C8.1, U6.40 (SIM_RST), U$1.C2 (RST)
UART_CTS: U2.4 (A2); also elsewhere on the board
UART_RTS: U2.3 (A1); also elsewhere on the board
UART_RXD: U2.6 (A4); also elsewhere on the board
UART_TXD: U2.5 (A3); also elsewhere on the board
VSIM: C7.1, C9.1, U6.41 (VSIM), U$1.C1 (VCC)
V_INT: C1.1, U2.15 (VCCB), U6.4 (V_INT)

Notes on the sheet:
Uni-Directional Voltage Translation
LTE CAT M1 / NB-IOT Module
Cell GPIO LEDs
SIM Card
NEED TO ADD ESD
